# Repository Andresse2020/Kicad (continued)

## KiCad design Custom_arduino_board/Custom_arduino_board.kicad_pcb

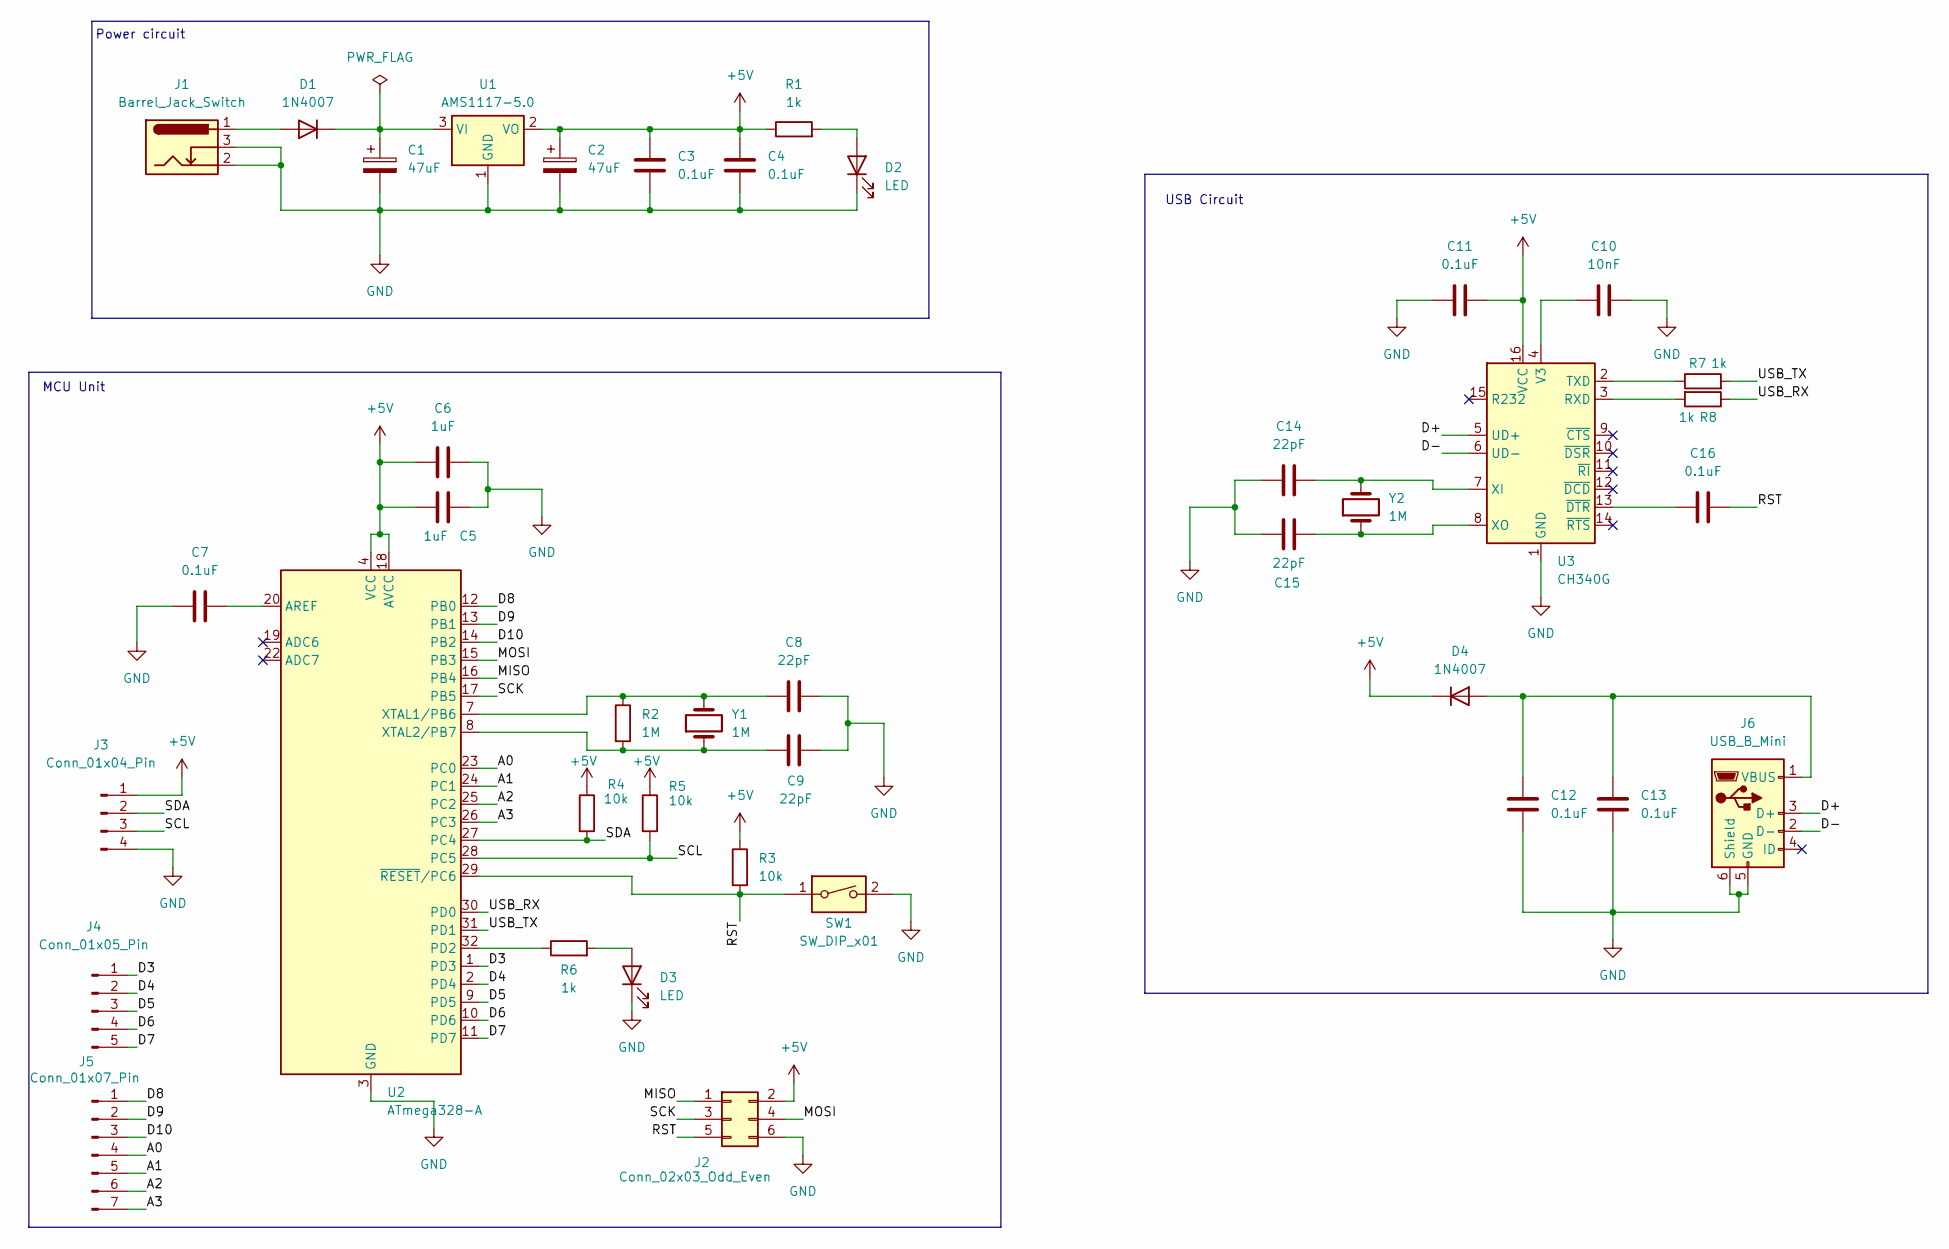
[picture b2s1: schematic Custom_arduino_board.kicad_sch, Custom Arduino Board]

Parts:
C1, C2: 47uF; CP_Elec_6.3x5.4
C3, C4, C7, C11, C12, C13, C16: 0.1uF; C_0805_2012Metric
C5, C6: 1uF; C_0805_2012Metric
C8, C9, C14, C15: 22pF; C_0805_2012Metric
C10: 10nF; C_0805_2012Metric
D1, D4: 1N4007; D_SOD-123
D2, D3: LED; LED_0603_1608Metric
J1: Barrel_Jack_Switch; BarrelJack_Horizontal
J2: Conn_02x03_Odd_Even; PinHeader_2x03_P2.54mm_Vertical
J3: Conn_01x04_Pin; PinHeader_1x04_P2.54mm_Vertical
J4: Conn_01x05_Pin; PinHeader_1x05_P2.54mm_Vertical
J5: Conn_01x07_Pin; PinHeader_1x07_P2.54mm_Vertical
J6: USB_B_Mini; USB_Mini-B_Lumberg_2486_01_Horizontal
R1, R6, R7, R8: 1k; R_0805_2012Metric
R2: 1M; R_0805_2012Metric
R3, R4, R5: 10k; R_0805_2012Metric
SW1: SW_DIP_x01; SW_PUSH_6mm
U1: AMS1117-5.0; SOT-223-3_TabPin2
U2: ATmega328-A; TQFP-32_7x7mm_P0.8mm
U3: CH340G; SOIC-16_3.9x9.9mm_P1.27mm
Y1, Y2: 1M; Crystal_HC49-4H_Vertical

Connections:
+5V: C2.1, C3.1, C4.1, C5.1, C6.2, C11.1, D4.1 (K), J2.2, J3.1, R1.1, R3.1, R4.1, R5.1, U1.2 (VO), U2.4 (VCC), U2.6 (VCC), U2.18 (AVCC), U3.16 (VCC)
/A0: J5.4, U2.23 (PC0)
/A1: J5.5, U2.24 (PC1)
/A2: J5.6, U2.25 (PC2)
/A3: J5.7, U2.26 (PC3)
/D3: J4.1, U2.1 (PD3)
/D4: J4.2, U2.2 (PD4)
/D5: J4.3, U2.9 (PD5)
/D6: J4.4, U2.10 (PD6)
/D7: J4.5, U2.11 (PD7)
/D8: J5.1, U2.12 (PB0)
/D9: J5.2, U2.13 (PB1)
/D10: J5.3, U2.14 (PB2)
/D+: J6.3 (D+), U3.5 (UD+)
/D-: J6.2 (D-), U3.6 (UD-)
/MISO: J2.1, U2.16 (PB4)
/MOSI: J2.4, U2.15 (PB3)
/RST: C16.1, J2.5, R3.2, SW1.1, U2.29 (~RESET/PC6)
/SCK: J2.3, U2.17 (PB5)
/SCL: J3.3, R5.2, U2.28 (PC5)
/SDA: J3.2, R4.2, U2.27 (PC4)
/USB_RX: R8.1, U2.30 (PD0)
/USB_TX: R7.2, U2.31 (PD1)
GND: C1.2, C2.2, C3.2, C4.2, C5.2, C6.1, C7.1, C8.2, C9.2, C10.1, C11.2, C12.2, C13.2, C14.1, C15.2, D2.1 (K), D3.1 (K), J1.2, J1.3, J2.6, J3.4, J6.5 (GND), J6.6 (Shield), SW1.2, U1.1 (GND), U2.3 (GND), U2.5 (GND), U2.21 (GND), U3.1 (GND)
unnamed: D1.2 (A), J1.1
unnamed: C1.1, D1.1 (K), U1.3 (VI)
unnamed: D2.2 (A), R1.2
unnamed: D3.2 (A), R6.2
unnamed: C12.1, C13.1, D4.2 (A), J6.1 (VBUS)
unnamed: C7.2, U2.20 (AREF)
unnamed: R6.1, U2.32 (PD2)
unnamed: C8.1, R2.1, U2.7 (XTAL1/PB6), Y1.2
unnamed: C9.1, R2.2, U2.8 (XTAL2/PB7), Y1.1
unnamed: R8.2, U3.3 (RXD)
unnamed: R7.1, U3.2 (TXD)
unnamed: C10.2, U3.4 (V3)
unnamed: C14.2, U3.7 (XI), Y2.2
unnamed: C15.1, U3.8 (XO), Y2.1
unnamed: C16.2, U3.13 (~DTR)

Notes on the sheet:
Power circuit
MCU Unit
USB Circuit

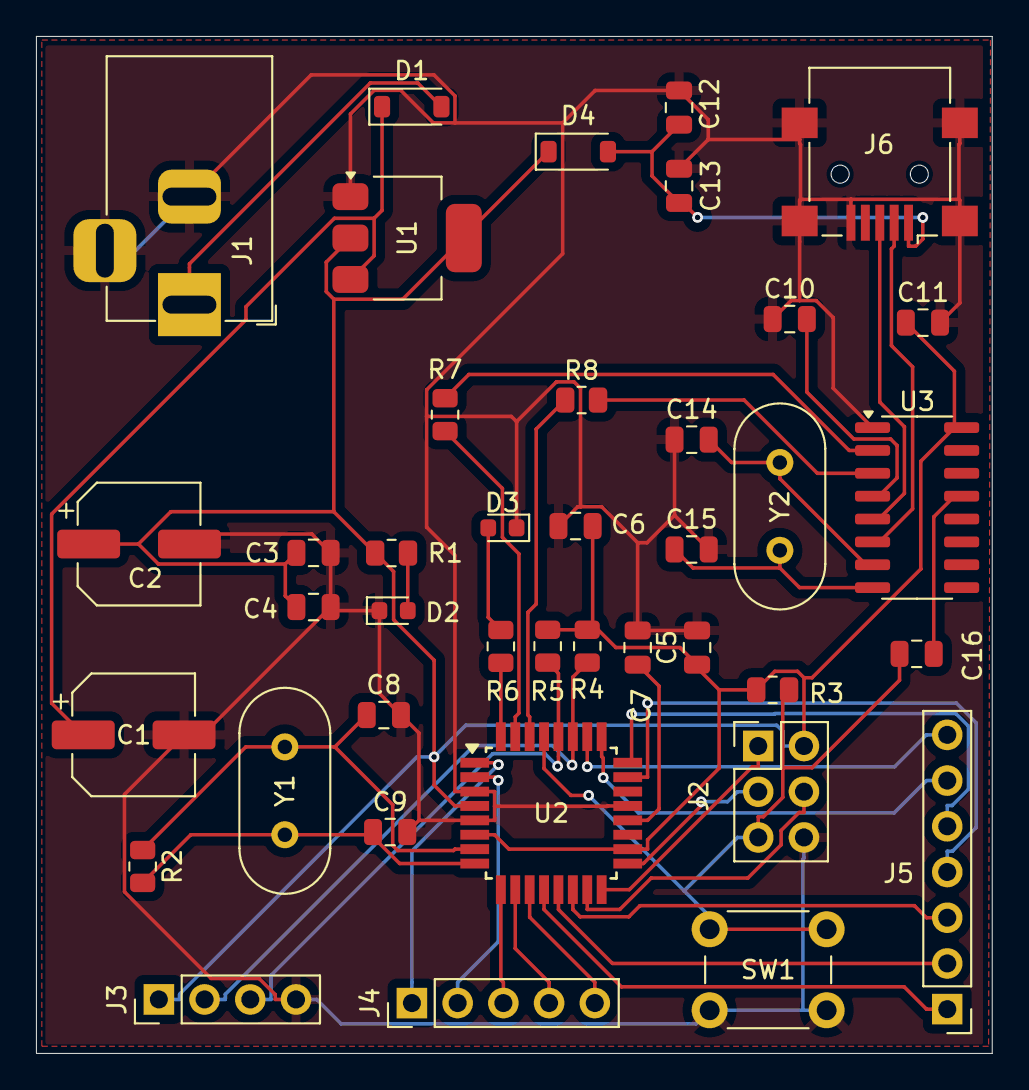
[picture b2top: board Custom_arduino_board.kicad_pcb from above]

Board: 2 copper layers, 53.1 x 56.5 mm, 40 parts (0 on the bottom side), 39 nets.

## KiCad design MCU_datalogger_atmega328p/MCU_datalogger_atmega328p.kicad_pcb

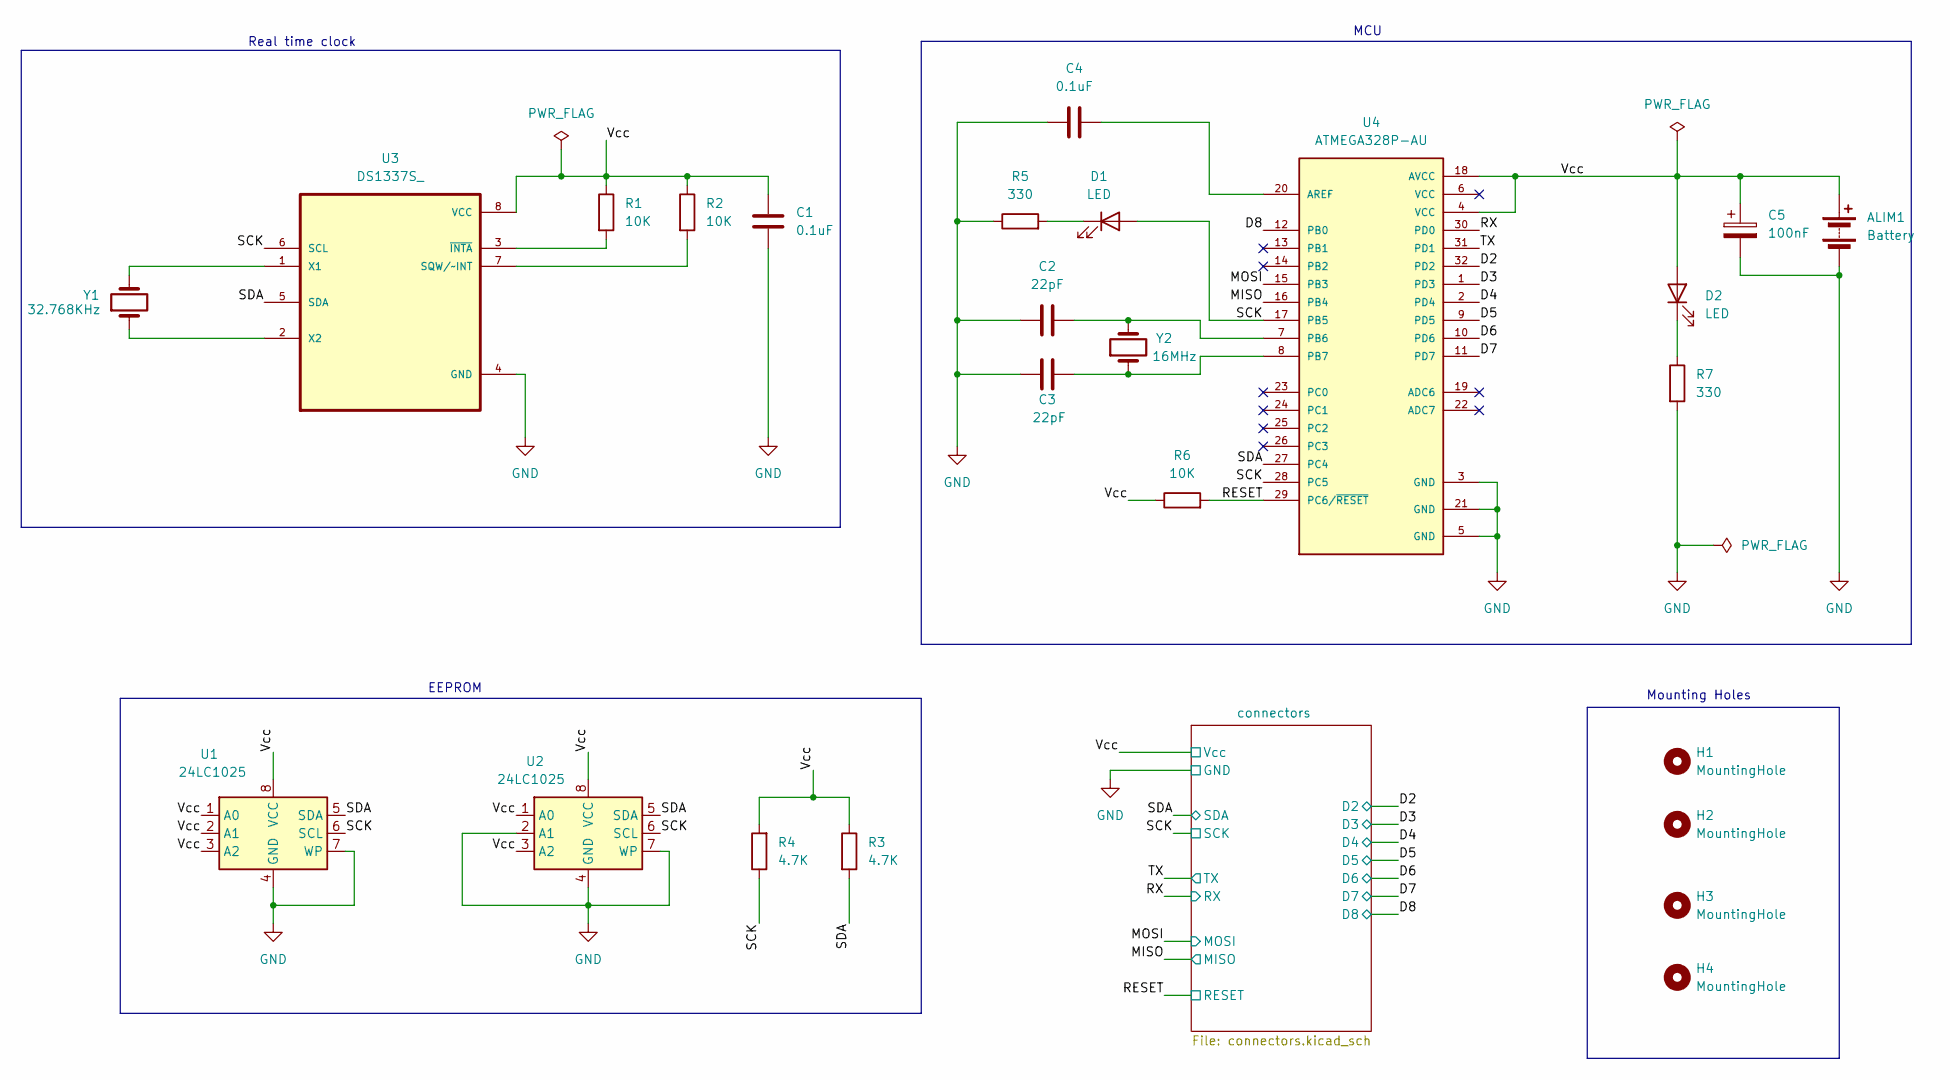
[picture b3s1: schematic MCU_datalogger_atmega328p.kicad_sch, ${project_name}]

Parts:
ALIM1: Battery; PinHeader_1x02_P2.54mm_Vertical
C1, C4: 0.1uF; C_0805_2012Metric
C2, C3: 22pF; C_0805_2012Metric
C5: 100nF; C_0805_2012Metric
D1, D2: LED; LED_0805_2012Metric
H1, H2, H3, H4: MountingHole; MountingHole_2.1mm
R1, R2, R6: 10K; R_0805_2012Metric
R3, R4: 4.7K; R_0805_2012Metric
R5, R7: 330; R_0805_2012Metric
U1, U2: 24LC1025; SOIC-8_5.23x5.23mm_P1.27mm
U3: DS1337S_; SOIC127P600X175-8N
U4: ATMEGA328P-AU; QFP80P900X900X120-32N; PARTREV 8271A
Y1: 32.768KHz; Crystal_SMD_5032-2Pin_5.0x3.2mm_HandSoldering
Y2: 16MHz; Crystal_SMD_5032-2Pin_5.0x3.2mm_HandSoldering

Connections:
/D2: U4.32 (PD2); also elsewhere on the board
/D3: U4.1 (PD3); also elsewhere on the board
/D4: U4.2 (PD4); also elsewhere on the board
/D5: U4.9 (PD5); also elsewhere on the board
/D6: U4.10 (PD6); also elsewhere on the board
/D7: U4.11 (PD7); also elsewhere on the board
/D8: U4.12 (PB0); also elsewhere on the board
/MISO: U4.16 (PB4); also elsewhere on the board
/MOSI: U4.15 (PB3); also elsewhere on the board
/RESET: R6.2, U4.29 (PC6/~RESET); also elsewhere on the board
/RX: U4.30 (PD0); also elsewhere on the board
/SCK: D1.2 (A), R4.1, U1.6 (SCL), U2.6 (SCL), U3.6 (SCL), U4.17 (PB5), U4.28 (PC5); also elsewhere on the board
/SDA: R3.2, U1.5 (SDA), U2.5 (SDA), U3.5 (SDA), U4.27 (PC4); also elsewhere on the board
/TX: U4.31 (PD1); also elsewhere on the board
/Vcc: ALIM1.1 (+), C1.1, C5.1, D2.2 (A), R1.1, R2.1, R3.1, R4.2, R6.1, U1.1 (A0), U1.2 (A1), U1.3 (A2), U1.8 (VCC), U2.1 (A0), U2.3 (A2), U2.8 (VCC), U3.8 (VCC), U4.4 (VCC), U4.18 (AVCC); also elsewhere on the board
GND: ALIM1.2 (-), C1.2, C2.1, C3.1, C4.1, C5.2, R5.1, R7.2, U1.4 (GND), U1.7 (WP), U2.2 (A1), U2.4 (GND), U2.7 (WP), U3.4 (GND), U4.3 (GND), U4.5 (GND), U4.21 (GND); also elsewhere on the board
unnamed: D1.1 (K), R5.2
unnamed: D2.1 (K), R7.1
unnamed: R2.2, U3.7 (SQW/~INT)
unnamed: U3.1 (X1), Y1.2
unnamed: U3.2 (X2), Y1.1
unnamed: R1.2, U3.3 (~INTA)
unnamed: C4.2, U4.20 (AREF)
unnamed: C2.2, U4.7 (PB6), Y2.2
unnamed: C3.2, U4.8 (PB7), Y2.1

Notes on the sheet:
EEPROM
MCU
Mounting Holes
Real time clock

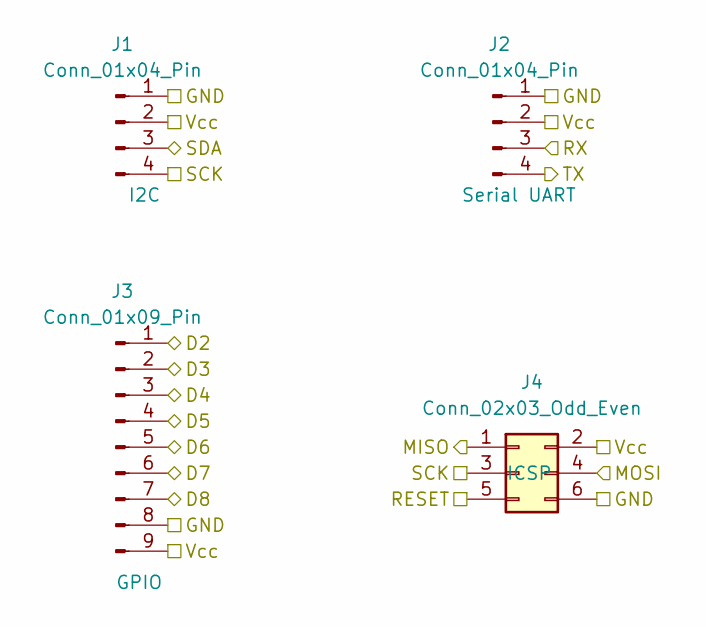
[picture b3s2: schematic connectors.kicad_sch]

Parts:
J1, J2: Conn_01x04_Pin; PinHeader_1x04_P2.54mm_Vertical
J3: Conn_01x09_Pin; PinHeader_1x09_P2.54mm_Vertical
J4: Conn_02x03_Odd_Even; PinHeader_2x03_P2.54mm_Vertical

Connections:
/D2: J3.1; also elsewhere on the board
/D3: J3.2; also elsewhere on the board
/D4: J3.3; also elsewhere on the board
/D5: J3.4; also elsewhere on the board
/D6: J3.5; also elsewhere on the board
/D7: J3.6; also elsewhere on the board
/D8: J3.7; also elsewhere on the board
/MISO: J4.1; also elsewhere on the board
/MOSI: J4.4; also elsewhere on the board
/RESET: J4.5; also elsewhere on the board
/RX: J2.3; also elsewhere on the board
/SCK: J1.4, J4.3; also elsewhere on the board
/SDA: J1.3; also elsewhere on the board
/TX: J2.4; also elsewhere on the board
/Vcc: J1.2, J2.2, J3.9, J4.2; also elsewhere on the board
GND: J1.1, J2.1, J3.8, J4.6; also elsewhere on the board

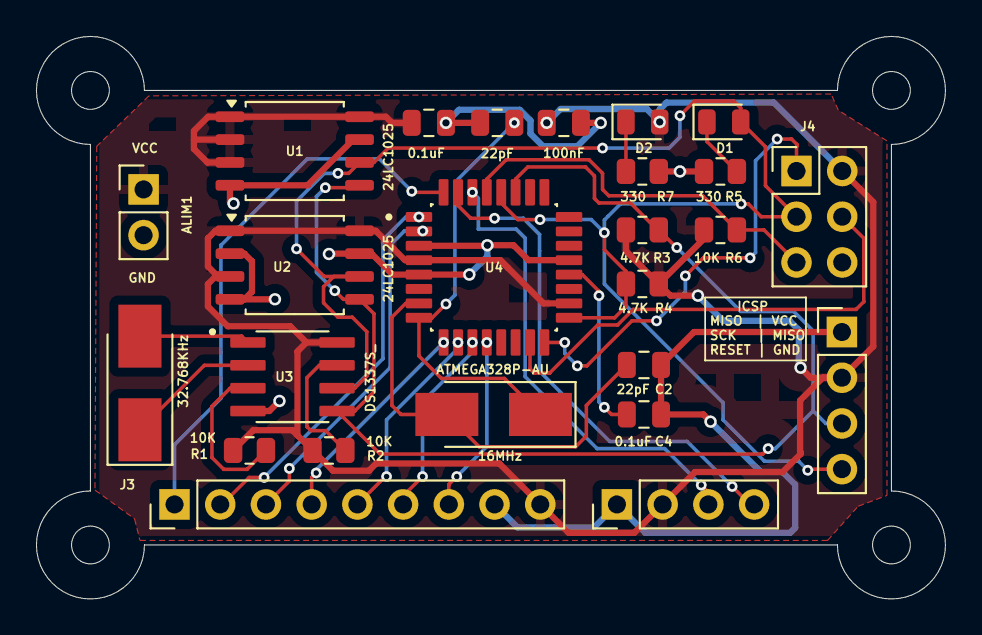
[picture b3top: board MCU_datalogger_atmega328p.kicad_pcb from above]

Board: 2 copper layers, 50.5 x 31.2 mm, 29 parts (0 on the bottom side), 25 nets.

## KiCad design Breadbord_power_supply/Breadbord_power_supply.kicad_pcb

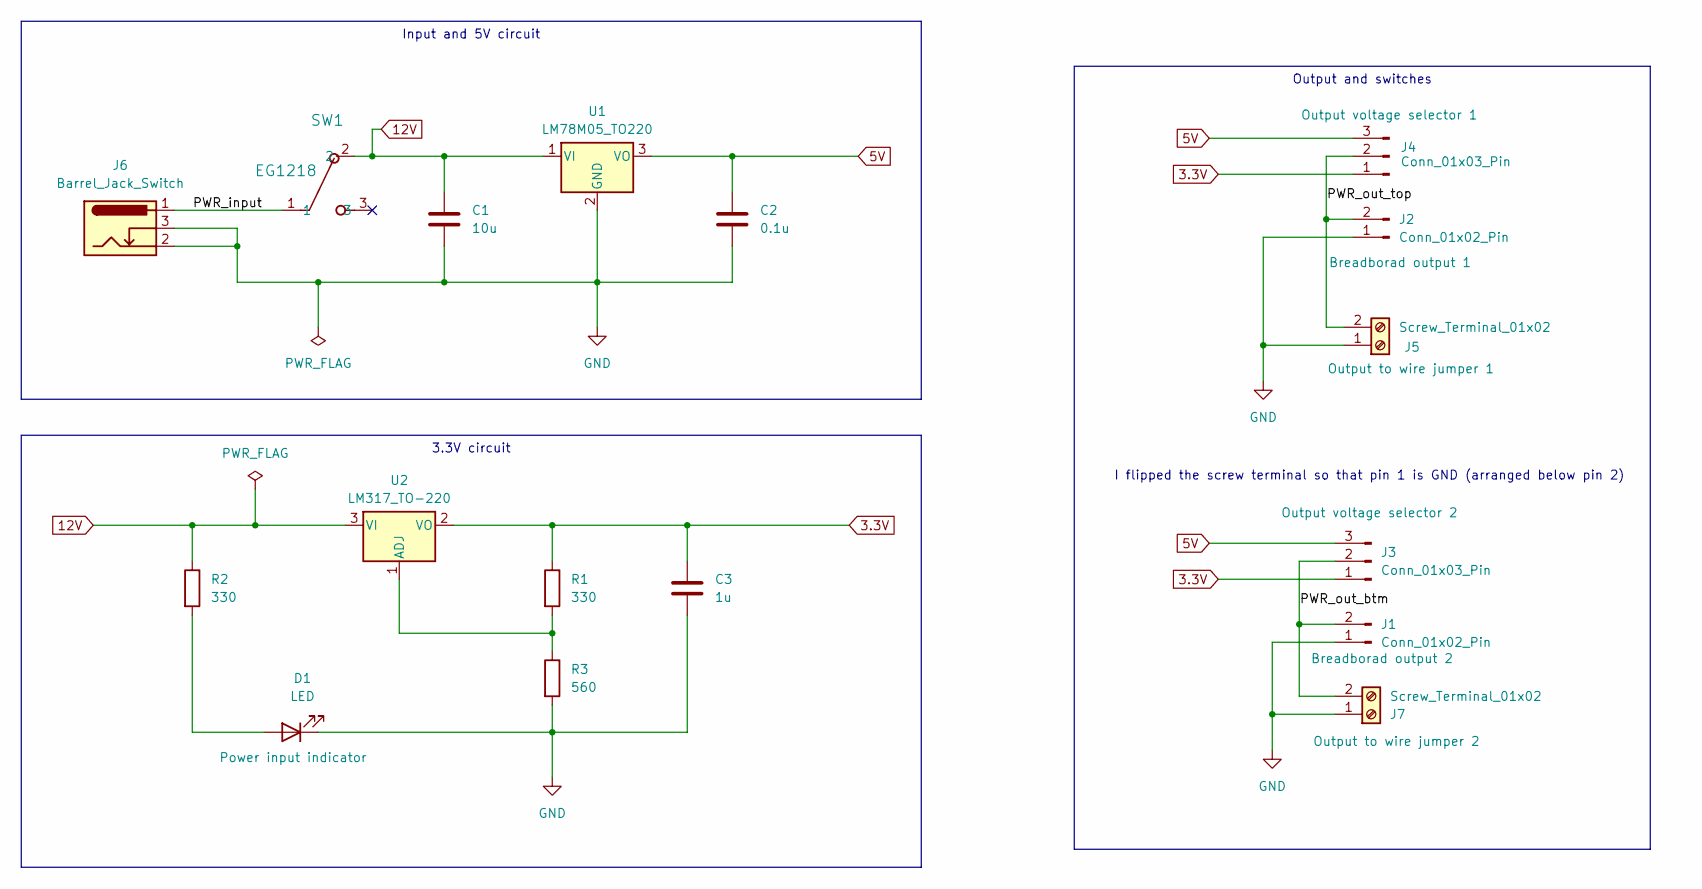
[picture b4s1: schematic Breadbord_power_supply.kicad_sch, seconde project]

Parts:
C1: 10u; C_Disc_D3.0mm_W1.6mm_P2.50mm
C2: 0.1u; C_Disc_D3.0mm_W1.6mm_P2.50mm
C3: 1u; C_Disc_D3.0mm_W1.6mm_P2.50mm
D1: LED; LED_D5.0mm
J1, J2: Conn_01x02_Pin; PinHeader_1x02_P2.54mm_Vertical
J3, J4: Conn_01x03_Pin; PinHeader_1x03_P2.54mm_Vertical
J5, J7: Screw_Terminal_01x02; TerminalBlock_Phoenix_MKDS-1,5-2-5.08_1x02_P5.08mm_Horizont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
J6: Barrel_Jack_Switch; BarrelJack_Horizontal
R1, R2: 330; R_Axial_DIN0204_L3.6mm_D1.6mm_P7.62mm_Horizontal
R3: 560; R_Axial_DIN0204_L3.6mm_D1.6mm_P7.62mm_Horizontal
SW1: EG1218; SW_1218_EWI
U1: LM78M05_TO220; TO-220-3_Vertical
U2: LM317_TO-220; TO-220-3_Vertical

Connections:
3.3V: C3.1, J3.1, J4.1, R1.1, U2.2 (VO)
5V: C2.1, J3.3, J4.3, U1.3 (VO)
12V: C1.1, R2.1, SW1.2, U1.1 (VI), U2.3 (VI)
/PWR_input: J6.1, SW1.1
/PWR_out_btm: J1.2, J3.2, J7.2
/PWR_out_top: J2.2, J4.2, J5.2
GND: C1.2, C2.2, C3.2, D1.1 (K), J1.1, J2.1, J5.1, J6.2, J6.3, J7.1, R3.2, U1.2 (GND)
unnamed: D1.2 (A), R2.2
unnamed: R1.2, R3.1, U2.1 (ADJ)

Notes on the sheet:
Input and 5V circuit
3.3V circuit
Output and switches
I flipped the screw terminal so that pin 1 is GND (arranged below pin 2)

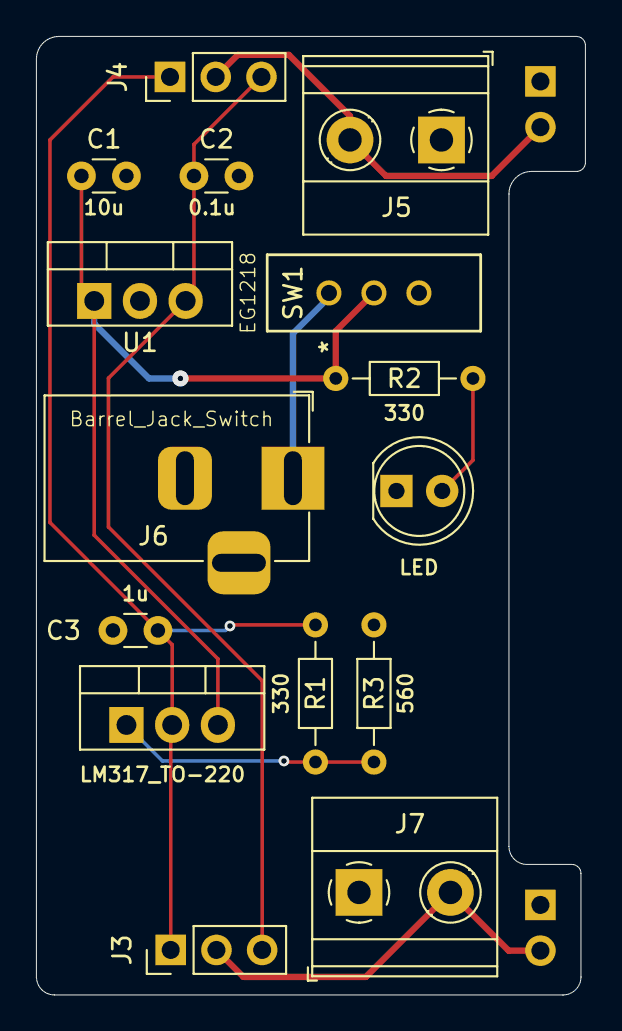
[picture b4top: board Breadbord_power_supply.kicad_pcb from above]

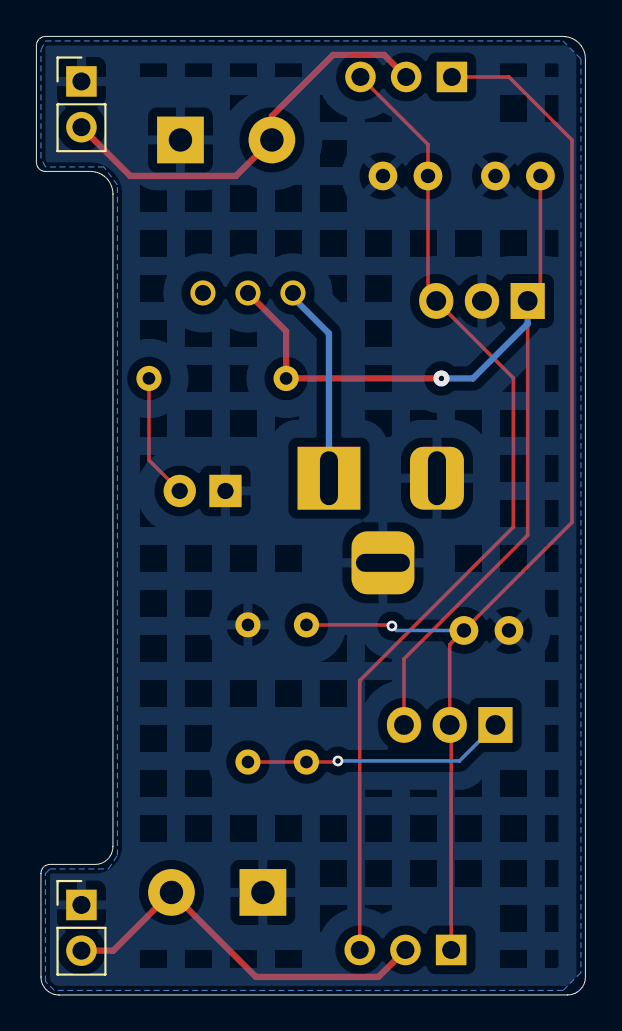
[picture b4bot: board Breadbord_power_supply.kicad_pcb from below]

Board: 2 copper layers, 30.5 x 53.2 mm, 17 parts (2 on the bottom side), 9 nets.

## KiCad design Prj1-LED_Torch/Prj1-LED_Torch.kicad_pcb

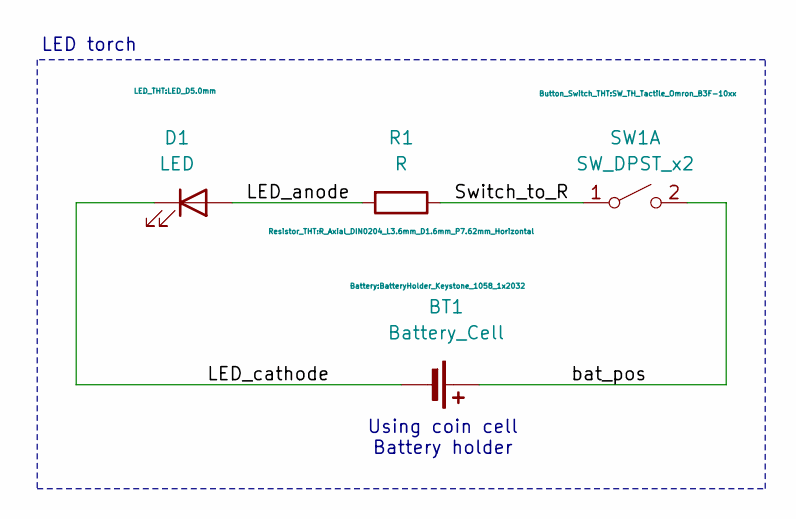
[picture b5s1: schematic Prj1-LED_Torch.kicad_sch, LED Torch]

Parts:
BT1: Battery_Cell; BatteryHolder_Keystone_1058_1x2032
D1: LED; LED_D5.0mm
R1: R; R_Axial_DIN0204_L3.6mm_D1.6mm_P7.62mm_Horizontal
SW1: SW_DPST_x2; SW_TH_Tactile_Omron_B3F-10xx

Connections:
/LED_anode: D1.2 (A), R1.2
/LED_cathode: BT1.2 (-), D1.1 (K)
/Switch_to_R: R1.1, SW1.1 (A)
/bat_pos: BT1.1 (+), SW1.2 (B)

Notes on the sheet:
LED torch
Using coin cell Battery holder

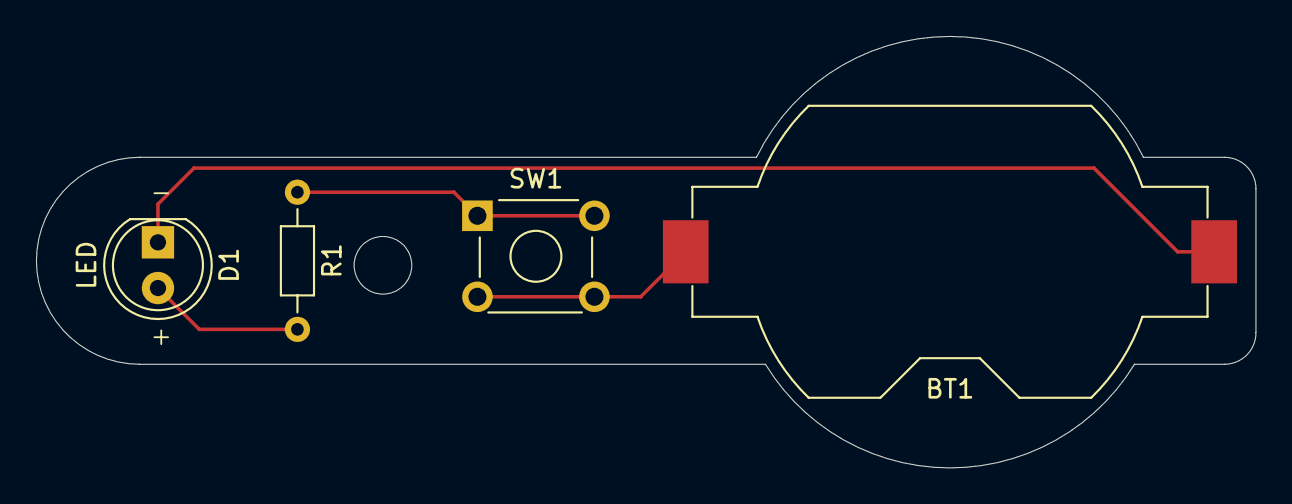
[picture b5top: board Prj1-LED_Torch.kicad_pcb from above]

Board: 2 copper layers, 67.8 x 24.0 mm, 4 parts (0 on the bottom side), 4 nets.

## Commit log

2024-06-07 Initialization
2024-06-12 MCU datalogger terminated
2024-06-13 MCU datalogger 4 layer version
2024-08-13 Custom Arduiono Board
2024-09-19 Interfaces
2024-09-25 Fin du projet
